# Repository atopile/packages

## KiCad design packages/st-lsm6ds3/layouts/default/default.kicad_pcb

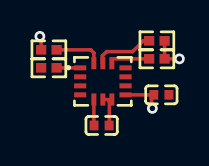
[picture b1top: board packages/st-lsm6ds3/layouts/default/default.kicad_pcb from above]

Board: 2 copper layers, 7 parts (0 on the bottom side), 6 nets.

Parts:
C2: 100nF; C0402
R1, R5: 10kΩ; R0402
R2: 100nF; C0402
R3, R4: 4.7kΩ; R0402
U1: LGA-14_L3.0-W2.5-P0.50-TL

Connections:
1: R5.2, U1.1
CS: R1.2, U1.12
SCL: R3.1, U1.13
SDA: R4.1, U1.14
hv: C2.1, R1.1, R2.1, R3.2, R4.2, U1.5, U1.8
lv: C2.2, R2.2, R5.1, U1.6, U1.7

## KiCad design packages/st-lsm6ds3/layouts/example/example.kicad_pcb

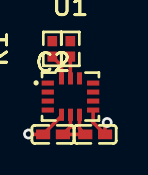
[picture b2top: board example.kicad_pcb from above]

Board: 2 copper layers, 5 parts (0 on the bottom side), 5 nets.

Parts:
C1, C2: 100nF ±10% 16V X7R; C0402
R1, R2: 10kΩ ±1% 62.5mW; R0402
U1: LGA-14_L3.0-W2.5-P0.50-TL

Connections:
SCL: R1.1, U1.13
SDA: R2.1, U1.14
gnd: C1.2, C2.2, U1.6, U1.7
hv: R1.2, R2.2
hv-1: C1.1, C2.1, U1.5, U1.8

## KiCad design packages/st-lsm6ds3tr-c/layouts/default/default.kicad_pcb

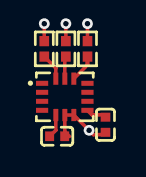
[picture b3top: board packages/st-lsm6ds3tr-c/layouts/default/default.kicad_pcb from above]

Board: 2 copper layers, 6 parts (0 on the bottom side), 5 nets.

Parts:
C1, C2: 1F; C0402
R1, R2, R3: 10000Ω; R0402
U1: LGA-14_L3.0-W2.5-P0.50-TL

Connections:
CS: R1.1, U1.12
SCL: R2.1, U1.13
SDA: R3.1, U1.14
hv: C1.1, C2.1, R1.2, R2.2, R3.2, U1.5, U1.8
lv: C1.2, C2.2, U1.1, U1.6, U1.7

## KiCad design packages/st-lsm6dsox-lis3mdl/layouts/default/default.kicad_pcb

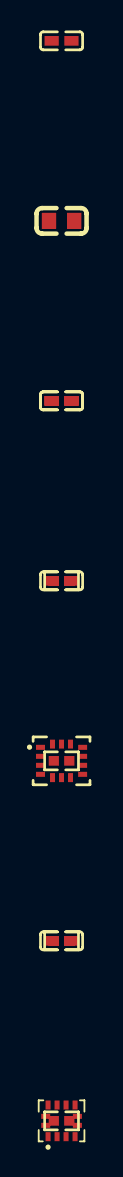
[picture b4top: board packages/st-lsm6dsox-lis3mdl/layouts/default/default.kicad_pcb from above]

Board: 2 copper layers, 12 parts (0 on the bottom side), 7 nets, no tracks yet.

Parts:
C1: 10µF ±20% 6.3V X5R; C0603
C2, C3, C4, C5, C6: 100nF ±10% 16V X7R; C0402
R1, R2, R3, R4: 10kΩ ±1% 62.5mW; R0402
U1: LGA-14L_L3.0-W2.5-P0.50-TL
U2: LGA-12_L2.0-W2.0-P0.50-BL

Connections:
C1: C4.1, U2.4
GND: C1.2, C2.2, C3.2, C4.2, C5.2, C6.2, U1.6, U1.7, U2.2, U2.3, U2.12
SCL: R1.2, U1.3, U1.13, U2.1
SDA: R2.2, U1.2, U1.14, U2.11
VCC: C1.1, C2.1, C3.1, C5.1, C6.1, R1.1, R2.1, R3.1, R4.1, U1.5, U1.8, U2.5, U2.6
footprint-CS-0: R4.2, U2.10
footprint-CS-1: R3.2, U1.12
